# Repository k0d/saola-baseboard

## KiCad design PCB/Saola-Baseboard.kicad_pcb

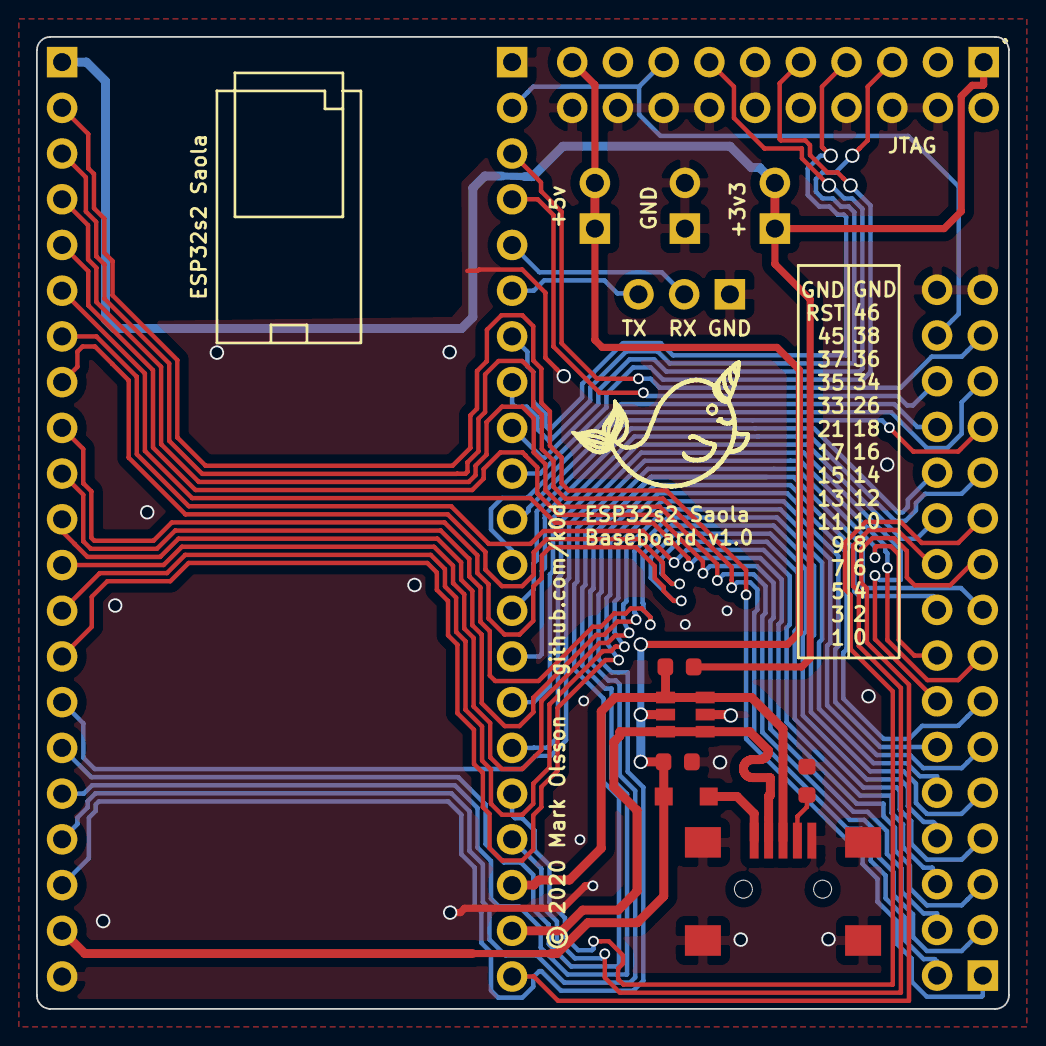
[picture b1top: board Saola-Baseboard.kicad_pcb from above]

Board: 2 copper layers, 54.0 x 54.0 mm, 15 parts (0 on the bottom side), 43 nets.

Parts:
C1: 100nF; C_0603_1608Metric
D1: BAT60A; D_SOD-323
J1: USB_B_Mini; USB_Mini-B_Socket
J2: UART; M_1x03_2.54_V
J3: GND; M_1x02_2.54_V
J4: 3v3; M_1x02_2.54_V
J5: 5v; M_1x02_2.54_V
J6: Conn_02x16_Odd_Even; M_2x16_2.54_V
J7: JTAG; M_2x10_2.54_V
J8, J9: Conn_01x21; F_1x21_2.54_V
R1: 100k; R_0603_1608Metric
R2: 1k5; R_0603_1608Metric
U1: USBLC6-2SC6; SOT-23-6
X1: Narwahl

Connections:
+3V3: J4.1, J4.2, J7.1, J8.1, R2.1
+5V: C1.1, D1.1, J5.1, J5.2, J7.19, J8.20, U1.5
/00: J6.1, J8.2
/01: J6.2, J8.3
/02: J6.3, J8.4
/03: J6.4, J8.5
/04: J6.5, J8.6
/05: J6.6, J8.7
/06: J6.7, J8.8
/07: J6.8, J8.9
/08: J6.9, J8.10
/09: J6.10, J8.11
/10: J6.11, J8.12
/11: J6.12, J8.13
/12: J6.13, J8.14
/13: J6.14, J8.15
/14: J6.15, J8.16
/15: J6.16, J8.17
/16: J6.17, J8.18
/17: J6.18, J8.19
/18: J6.19, J9.21
/19: J1.2, J9.20, U1.1, U1.6
/20: J1.3, J9.19, R2.2, U1.3, U1.4
/21: J6.20, J9.18
/26: J6.21, J9.17
/33: J6.22, J9.16
/34: J6.23, J9.15
/35: J6.24, J9.14
/36: J6.25, J9.13
/37: J6.26, J9.12
/38: J6.27, J9.11
/39: J7.9, J9.10
/40: J7.13, J9.9
/41: J7.5, J9.8
/42: J7.7, J9.7
/45: J6.28, J9.4
/46: J6.29, J9.3
/RST: J6.30, J7.15, J9.2
/RX: J2.2, J9.5
/TX: J2.3, J9.6
GND: C1.2, J1.5, J1.6, J2.1, J3.1, J3.2, J6.31, J6.32, J7.4, J7.6, J7.8, J7.10, J7.11, J7.12, J7.14, J7.16, J7.18, J7.20, J8.21, J9.1, R1.2, U1.2
unnamed: D1.2, J1.1
unnamed: J1.4, R1.1

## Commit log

2020-05-22 Updated silkscreen
2020-06-06 v1.0 release

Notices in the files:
PCB/Saola-Baseboard.kicad_pcb:
© 2020 Mark Olsson - github.com/k0d
